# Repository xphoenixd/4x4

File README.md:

4x4 choc spaced macropad.

solder the pro micro in on the bottom side. the square pin on the pcb is pin 1 (tx) on the pro micro.

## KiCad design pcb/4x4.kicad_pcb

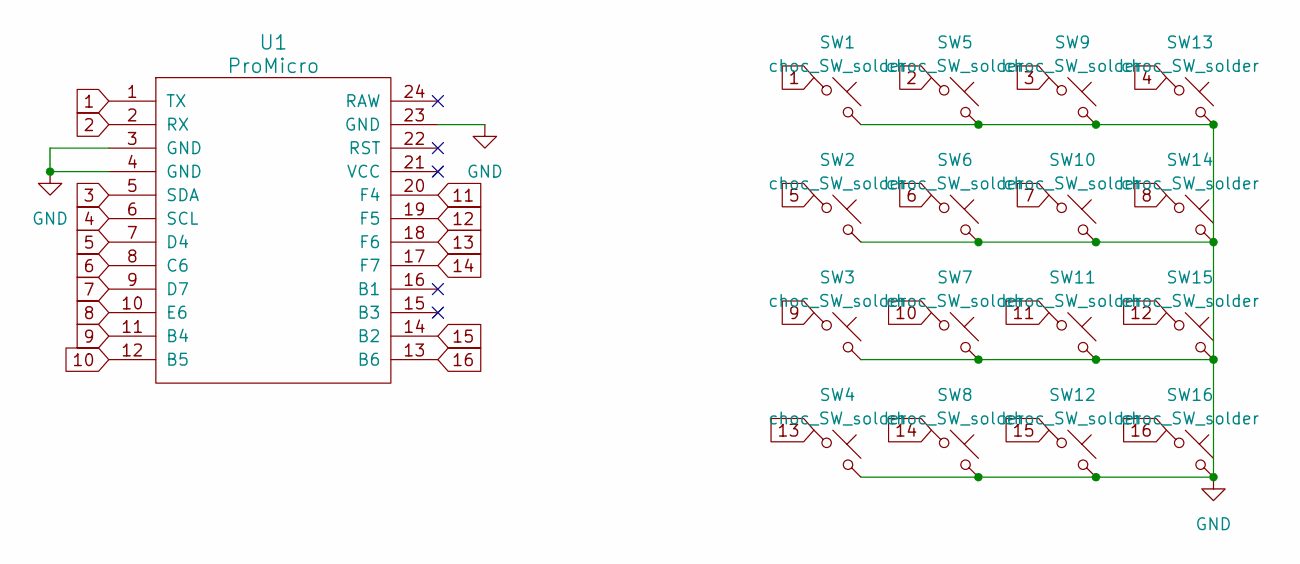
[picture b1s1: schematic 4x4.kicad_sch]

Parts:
SW1, SW2, SW3, SW4, SW5, SW6, SW7, SW8, SW9, SW10, SW11, SW12, SW13, SW14, SW15, SW16: choc_SW_solder; SW_choc_1u
U1: ProMicro

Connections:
1: SW1.1, U1.1 (TX)
2: SW5.1, U1.2 (RX)
3: SW9.1, U1.5 (SDA)
4: SW13.1, U1.6 (SCL)
5: SW2.1, U1.7 (D4)
6: SW6.1, U1.8 (C6)
7: SW10.1, U1.9 (D7)
8: SW14.1, U1.10 (E6)
9: SW3.1, U1.11 (B4)
10: SW7.1, U1.12 (B5)
11: SW11.1, U1.20 (F4)
12: SW15.1, U1.19 (F5)
13: SW4.1, U1.18 (F6)
14: SW8.1, U1.17 (F7)
15: SW12.1, U1.14 (B2)
16: SW16.1, U1.13 (B6)
GND: SW1.2, SW2.2, SW3.2, SW4.2, SW5.2, SW6.2, SW7.2, SW8.2, SW9.2, SW10.2, SW11.2, SW12.2, SW13.2, SW14.2, SW15.2, SW16.2, U1.3 (GND), U1.4 (GND), U1.23 (GND)

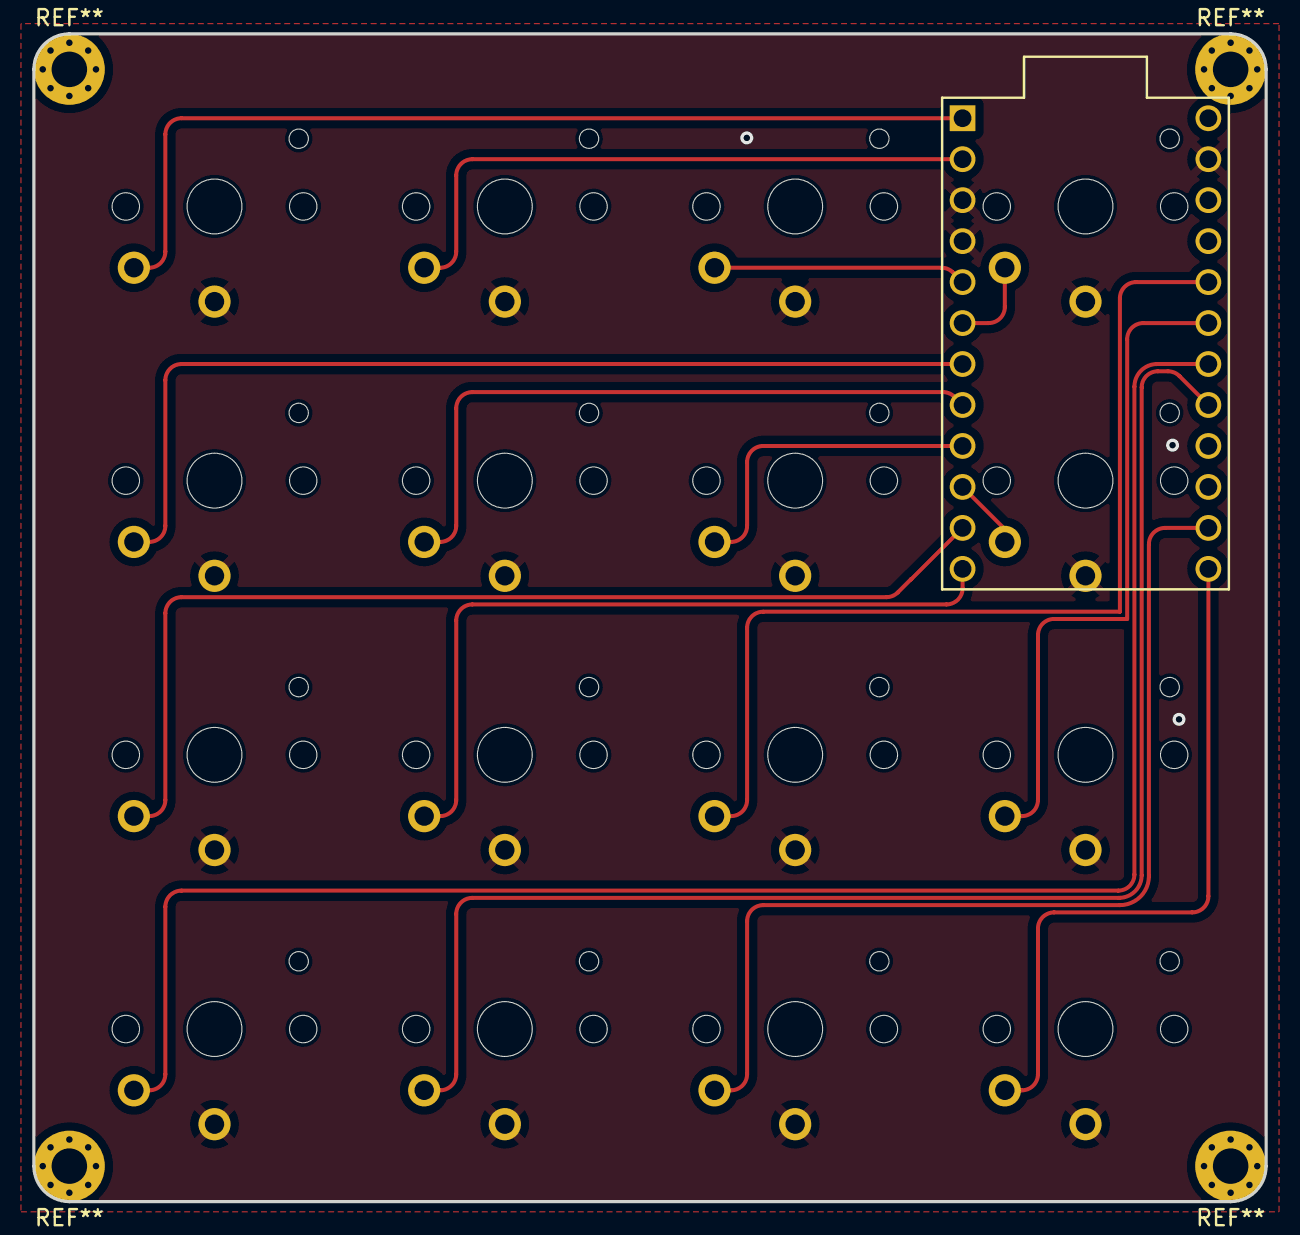
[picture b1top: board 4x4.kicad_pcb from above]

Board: 2 copper layers, 76.4 x 72.4 mm, 17 parts (0 on the bottom side), 17 nets.

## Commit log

2023-03-07 Finished PCB
2023-03-07 readme
2023-03-07 removed bottom plate gerbers from pcb folder
